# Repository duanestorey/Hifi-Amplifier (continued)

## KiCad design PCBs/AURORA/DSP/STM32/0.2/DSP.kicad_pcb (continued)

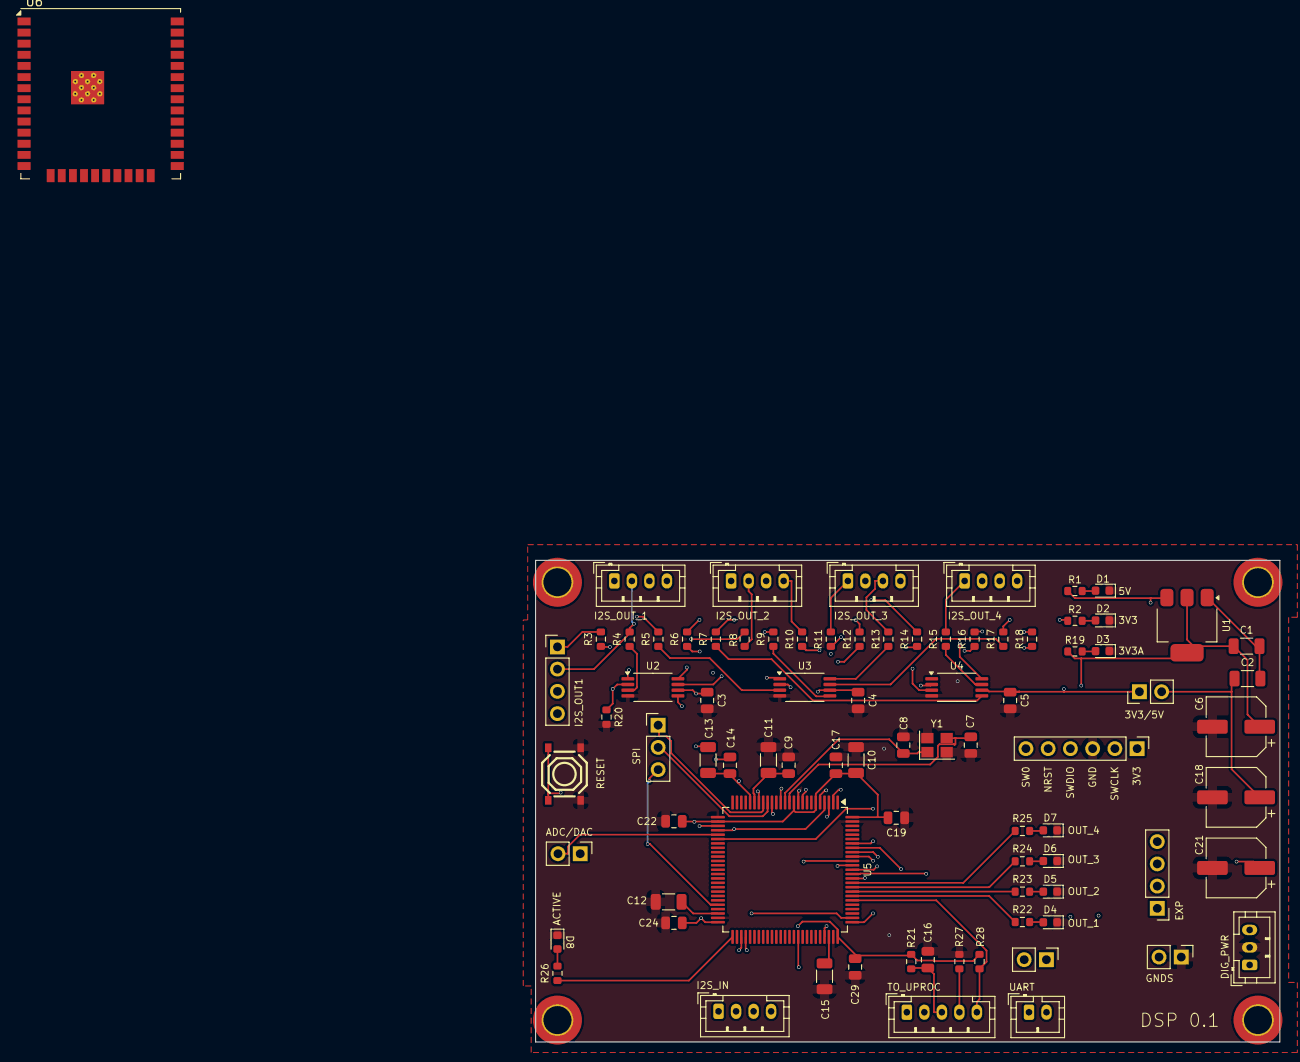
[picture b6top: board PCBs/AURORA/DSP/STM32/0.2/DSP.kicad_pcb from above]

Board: 4 copper layers, 85.0 x 55.0 mm, 87 parts (0 on the bottom side), 81 nets.

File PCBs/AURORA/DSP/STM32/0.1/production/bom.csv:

Designator,Footprint,Quantity,Value,LCSC Part #
"C1, C10, C11, C13, C2",1206,5,10u,C13585
"C12, C15",1206,2,2.2u,C50254
"C14, C16, C17, C19, C22, C24, C29, C3, C4, C5, C9",0805,11,0.1u,C28233
"C18, C21, C6",CP_Elec_6.3x7.7,3,220u,C4747974
"C7, C8",0805,2,20p,C1798
"D1, D2, D3, D4, D5, D6, D7, D8",0805,8,BLUE,C84259
"J1, J2, J3, J4, J7",JST_PH_B4B-PH-K_1x04_P2.00mm_Vertical,5,Conn_01x04_Pin,
"J10, J9",JST_PH_B2B-PH-K_1x02_P2.00mm_Vertical,2,Conn_01x02_Male,
"J11, J14, J15, J16, J17",PinHeader_1x02_P2.54mm_Vertical,5,Conn_01x02_Pin,C225477
"J12, J13, J18",PinHeader_1x04_P2.54mm_Vertical,3,Conn_01x04_Pin,C6332197
J5,PinHeader_1x06_P2.54mm_Vertical,1,Conn_01x06_Pin,C6332199
"J6, J8",JST_PH_B3B-PH-K_1x03_P2.00mm_Vertical,2,Conn_01x03_Pin,
"R1, R19, R2, R22, R23, R24, R25, R26",0603,8,150R,C22808
"R10, R11, R12, R13, R14, R15, R16, R17, R18, R3, R4, R5, R6, R7, R8, R9",0603,16,22R,C23345
"R20, R21, R27, R28",0603,4,4.7K,C23162
SW2,SW-SMD_4P-L5.1-W5.1-P3.70-LS6.5-TL_H1.5,1,TS-1187A-B-A-B,C318884
U1,SOT-223-3_TabPin2,1,AMS1117-3.3,C6186
"U2, U3, U4",TSSOP-8_4.4x3mm_P0.65mm,3,PI6CV304,C2649345
U5,LQFP-100_14x14mm_P0.5mm,1,STM32H723VGTx,C730142
Y1,Crystal_SMD_SeikoEpson_FA238-4Pin_3.2x2.5mm,1,25 MHz,C9006

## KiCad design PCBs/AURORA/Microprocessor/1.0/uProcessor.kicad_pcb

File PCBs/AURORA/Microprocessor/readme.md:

# Microprocessor Board

The heart of the amplifier is this microprocessor board based on the ESP32 WROOM 32 IC. Now supports a HAT.

## Version History

- 1.0: Initial Release
- 1.1: Addressed issue with ESP32 programming transistors
- 1.2: Added missing pull-down resistor for relay/softstart 

## Speciality Components

* ESP32 WROOM 32
* FT232RL USB to UART converter
* TMP100 temperature sensor

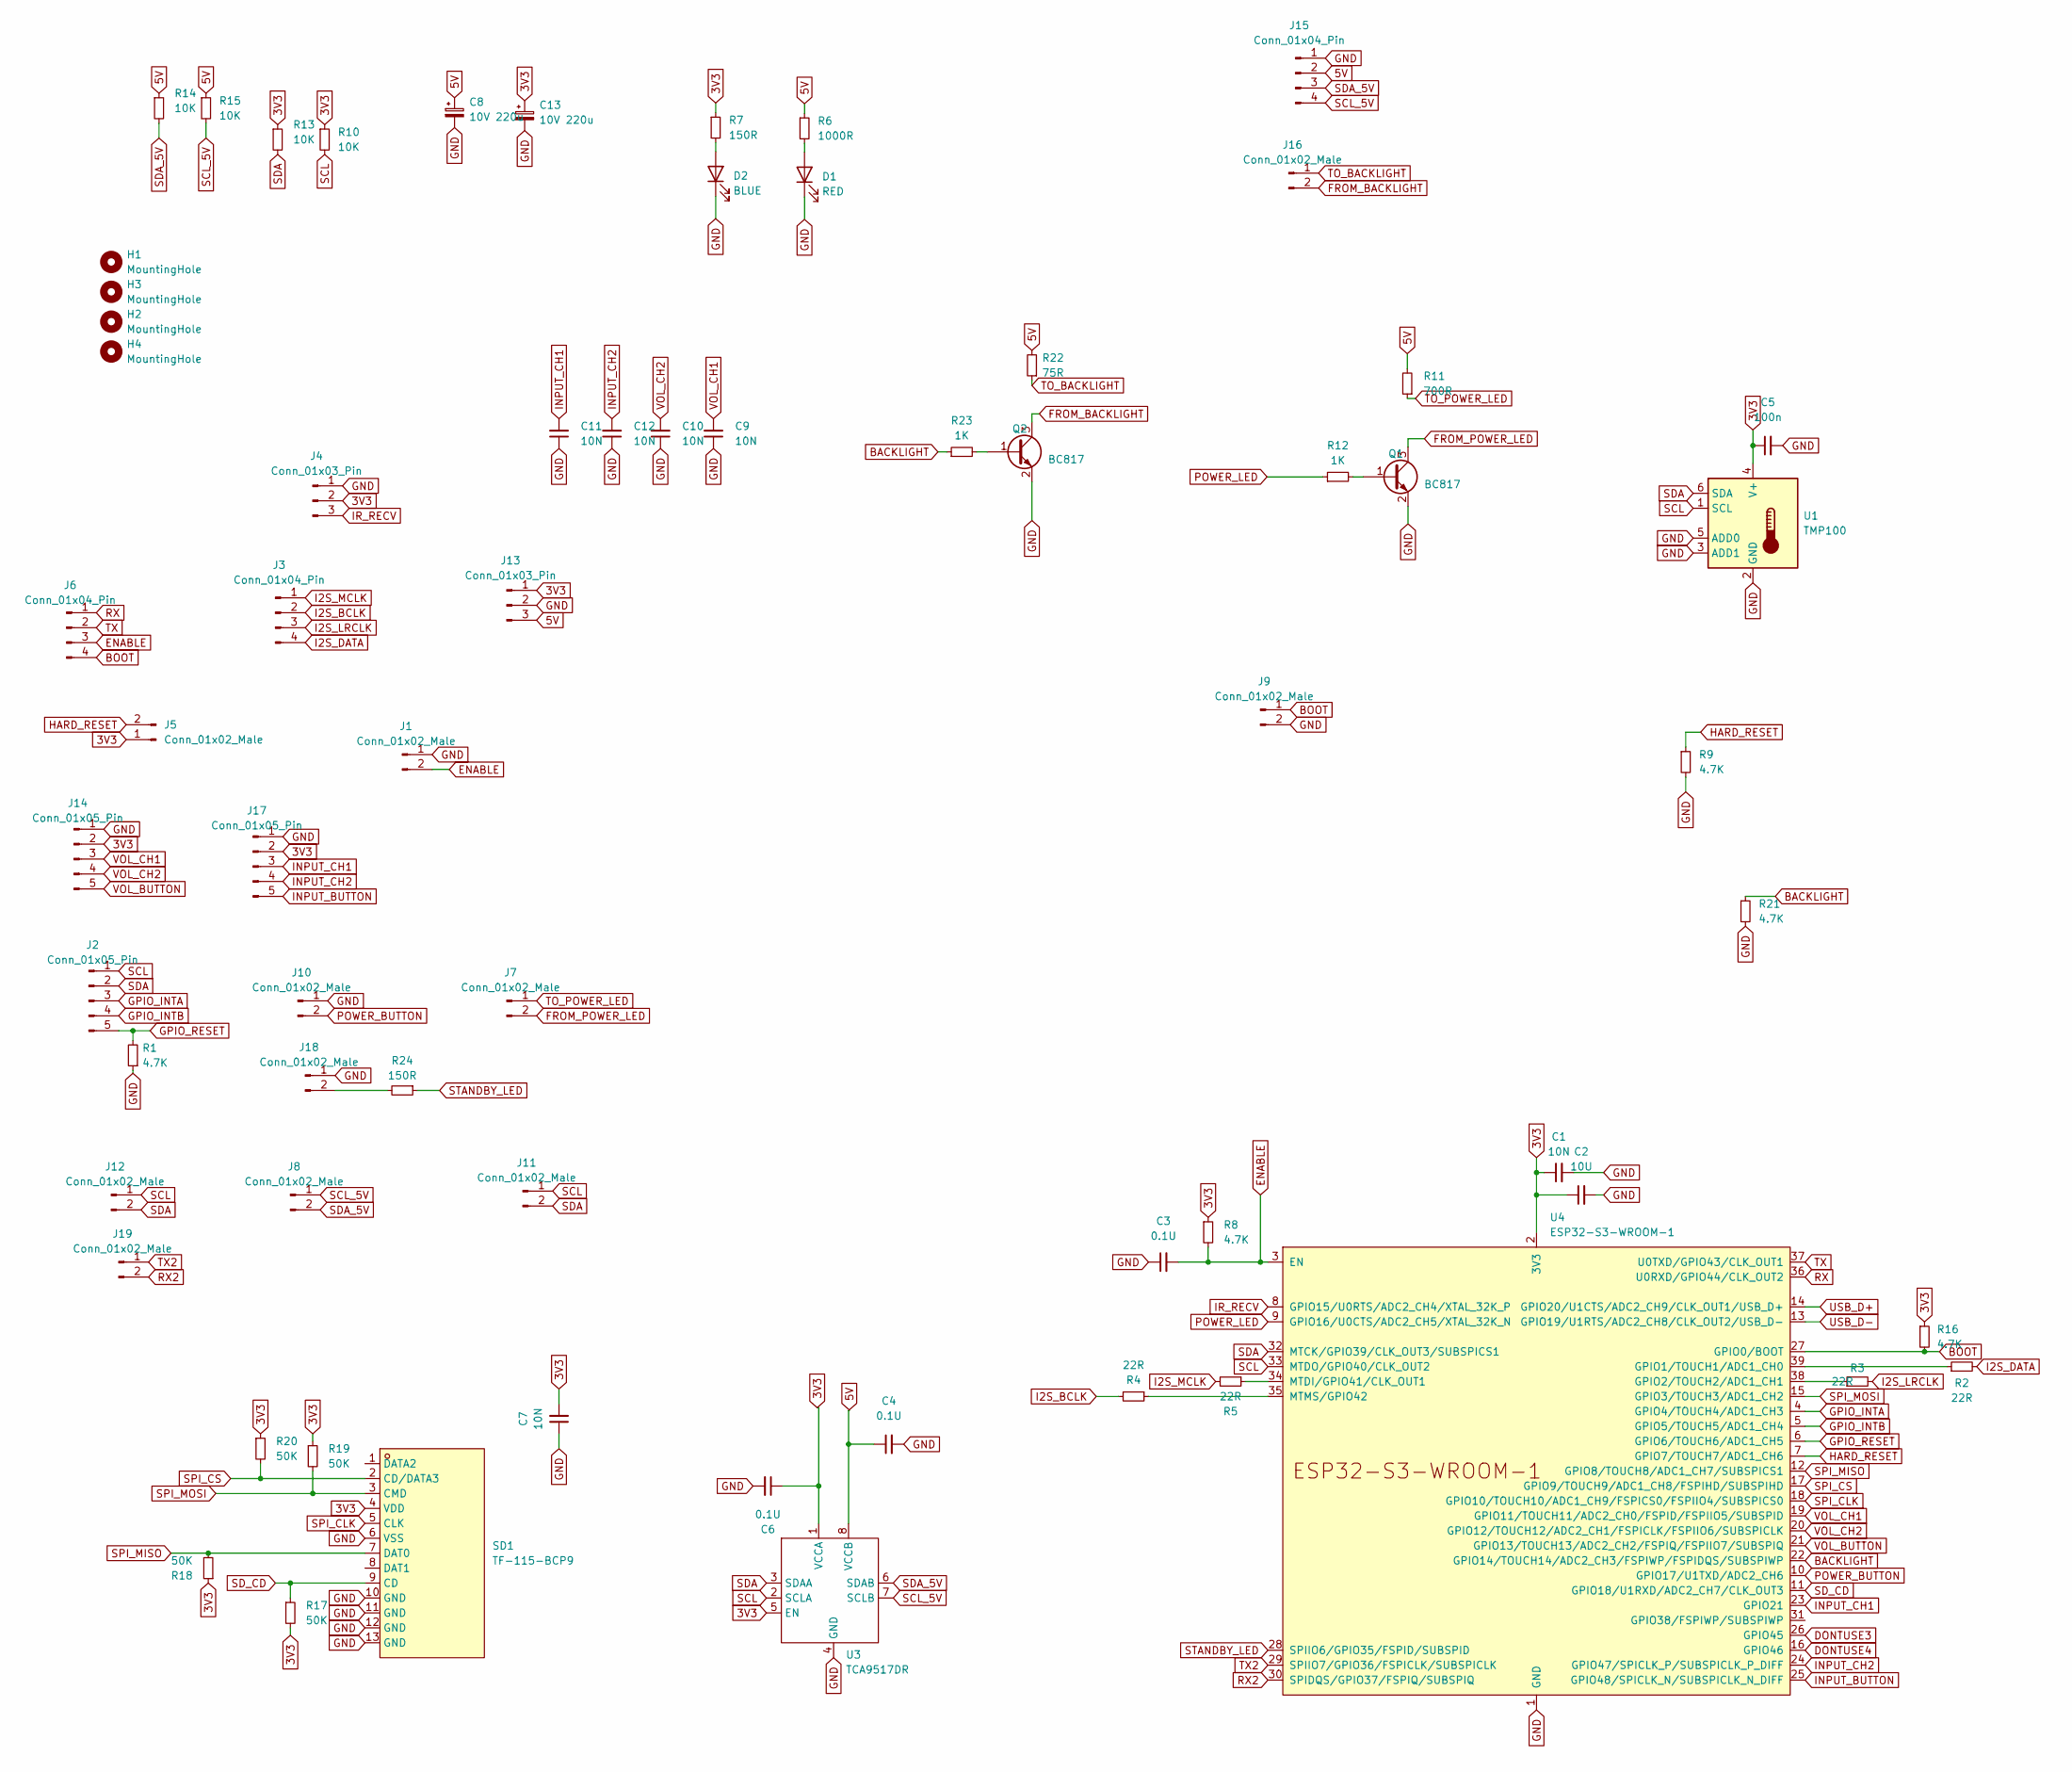
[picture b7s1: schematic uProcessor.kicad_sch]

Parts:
C1, C7: 10N; C_0805_2012Metric_Pad1.18x1.45mm_HandSolder
C2: 10U; C_1206_3216Metric_Pad1.33x1.80mm_HandSolder
C3, C4, C6: 0.1U; C_0805_2012Metric_Pad1.18x1.45mm_HandSolder
C5: 100n; C_0805_2012Metric_Pad1.18x1.45mm_HandSolder
C8, C13: 10V 220u; CP_Radial_D6.3mm_P2.50mm
C9, C10, C11, C12: 10N; C_0603_1608Metric_Pad1.08x0.95mm_HandSolder
D1: RED; LED_0603_1608Metric; LCSC XL-1608UBC-04
D2: BLUE; LED_0603_1608Metric; LCSC NCD0603R1
H1, H2, H3, H4: MountingHole; MountingHole_3.2mm_M3_DIN965_Pad_TopOnly
J1, J7, J8, J10, J11, J12, J16, J18, J19: Conn_01x02_Male; JST_PH_B2B-PH-K_1x02_P2.00mm_Vertical
J2, J14, J17: Conn_01x05_Pin; JST_PH_B5B-PH-K_1x05_P2.00mm_Vertical
J3, J6, J15: Conn_01x04_Pin; JST_PH_B4B-PH-K_1x04_P2.00mm_Vertical
J4, J13: Conn_01x03_Pin; JST_PH_B3B-PH-K_1x03_P2.00mm_Vertical
J5, J9: Conn_01x02_Male; PinHeader_1x02_P2.54mm_Vertical
Q1, Q2: BC817; TSOT-23; Mouser 637-BC817K-40
R1, R8, R9, R16, R21: 4.7K; R_0603_1608Metric_Pad0.98x0.95mm_HandSolder
R2, R3, R4, R5: 22R; R_0603_1608Metric; Mouser 603-RT0805FRE0722RL
R6: 1000R; R_0603_1608Metric_Pad0.98x0.95mm_HandSolder
R7, R24: 150R; R_0603_1608Metric_Pad0.98x0.95mm_HandSolder
R10, R13, R14, R15: 10K; R_0603_1608Metric_Pad0.98x0.95mm_HandSolder
R11: 700R; R_0603_1608Metric_Pad0.98x0.95mm_HandSolder
R12, R23: 1K; R_0603_1608Metric_Pad0.98x0.95mm_HandSolder
R17, R18, R19, R20: 50K; R_0603_1608Metric_Pad0.98x0.95mm_HandSolder
R22: 75R; R_0603_1608Metric_Pad0.98x0.95mm_HandSolder
SD1: TF-115-BCP9; TF-SMD_TF-115-BCP9; LCSC Part C720505
U1: TMP100; SOT-23-6
U3: TCA9517DR; SOIC-8_3.9x4.9mm_P1.27mm; Mouser 595-TCA9517DR
U4: ESP32-S3-WROOM-1

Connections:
3V3: C1.1, C2.1, C5.1, C6.1, C7.2, C13.1, J4.2, J5.1, J13.1, J14.2, J17.2, R7.1, R8.1, R10.1, R13.1, R16.1, R17.2, R18.1, R19.1, R20.1, SD1.4 (VDD), U1.4 (V+), U3.1 (VCCA), U3.5 (EN), U4.2 (3V3)
5V: C4.1, C8.1, J13.3, J15.2, R6.1, R11.2, R14.1, R15.1, R22.2, U3.8 (VCCB)
BACKLIGHT: R21.1, R23.1, U4.22 (GPIO14/TOUCH14/ADC2_CH3/FSPIWP/FSPIDQS/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)
BOOT: J6.4, J9.1, R16.2, U4.27 (GPIO0/BOOT)
DONTUSE3: U4.26 (GPIO45)
DONTUSE4: U4.16 (GPIO46)
ENABLE: C3.2, J1.2, J6.3, R8.2, U4.3 (EN)
FROM_BACKLIGHT: J16.2, Q2.3 (C)
FROM_POWER_LED: J7.2, Q1.3 (C)
GND: C1.2, C2.2, C3.1, C4.2, C5.2, C6.2, C7.1, C8.2, C9.1, C10.1, C11.1, C12.1, C13.2, D1.1 (K), D2.1 (K), J1.1, J4.1, J9.2, J10.1, J13.2, J14.1, J15.1, J17.1, J18.1, Q1.2 (E), Q2.2 (E), R1.1, R9.2, R21.2, SD1.6 (VSS), SD1.10 (GND), SD1.11 (GND), SD1.12 (GND), SD1.13 (GND), U1.2 (GND), U1.3 (ADD1), U1.5 (ADD0), U3.4 (GND), U4.1 (GND), U4.40 (GND), U4.41 (GND)
GPIO_INTA: J2.3, U4.4 (GPIO4/TOUCH4/ADC1_CH3)
GPIO_INTB: J2.4, U4.5 (GPIO5/TOUCH5/ADC1_CH4)
GPIO_RESET: J2.5, R1.2, U4.6 (GPIO6/TOUCH6/ADC1_CH5)
HARD_RESET: J5.2, R9.1, U4.7 (GPIO7/TOUCH7/ADC1_CH6)
I2S_BCLK: J3.2, R4.2
I2S_DATA: J3.4, R2.2
I2S_LRCLK: J3.3, R3.2
I2S_MCLK: J3.1, R5.2
INPUT_BUTTON: J17.5, U4.25 (GPIO48/SPICLK_N/SUBSPICLK_N_DIFF)
INPUT_CH1: C11.2, J17.3, U4.23 (GPIO21)
INPUT_CH2: C12.2, J17.4, U4.24 (GPIO47/SPICLK_P/SUBSPICLK_P_DIFF)
IR_RECV: J4.3, U4.8 (GPIO15/U0RTS/ADC2_CH4/XTAL_32K_P)
unnamed: D1.2 (A), R6.2
unnamed: D2.2 (A), R7.2
unnamed: J18.2, R24.2
unnamed: Q1.1 (B), R12.2
unnamed: Q2.1 (B), R23.2
unnamed: R2.1, U4.39 (GPIO1/TOUCH1/ADC1_CH0)
unnamed: R3.1, U4.38 (GPIO2/TOUCH2/ADC1_CH1)
unnamed: R5.1, U4.34 (MTDI/GPIO41/CLK_OUT1)
unnamed: R4.1, U4.35 (MTMS/GPIO42)
POWER_BUTTON: J10.2, U4.10 (GPIO17/U1TXD/ADC2_CH6)
POWER_LED: R12.1, U4.9 (GPIO16/U0CTS/ADC2_CH5/XTAL_32K_N)
RX: J6.1, U4.36 (U0RXD/GPIO44/CLK_OUT2)
RX2: J19.2, U4.30 (SPIDQS/GPIO37/FSPIQ/SUBSPIQ)
SCL: J2.1, J11.1, J12.1, R10.2, U1.1 (SCL), U3.2 (SCLA), U4.33 (MTDO/GPIO40/CLK_OUT2)
SCL_5V: J8.1, J15.4, R15.2, U3.7 (SCLB)
SDA: J2.2, J11.2, J12.2, R13.2, U1.6 (SDA), U3.3 (SDAA), U4.32 (MTCK/GPIO39/CLK_OUT3/SUBSPICS1)
SDA_5V: J8.2, J15.3, R14.2, U3.6 (SDAB)
SD_CD: R17.1, SD1.9 (CD), U4.11 (GPIO18/U1RXD/ADC2_CH7/CLK_OUT3)
SPI_CLK: SD1.5 (CLK), U4.18 (GPIO10/TOUCH10/ADC1_CH9/FSPICS0/FSPIIO4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)
SPI_CS: R20.2, SD1.2 (CD/DATA3), U4.17 (GPIO9/TOUCH9/ADC1_CH8/FSPIHD/SUBSPIHD)
SPI_MISO: R18.2, SD1.7 (DAT0), U4.12 (GPIO8/TOUCH8/ADC1_CH7/SUBSPICS1)
SPI_MOSI: R19.2, SD1.3 (CMD), U4.15 (GPIO3/TOUCH3/ADC1_CH2)
STANDBY_LED: R24.1, U4.28 (SPIIO6/GPIO35/FSPID/SUBSPID)
TO_BACKLIGHT: J16.1, R22.1
TO_POWER_LED: J7.1, R11.1
TX: J6.2, U4.37 (U0TXD/GPIO43/CLK_OUT1)
TX2: J19.1, U4.29 (SPIIO7/GPIO36/FSPICLK/SUBSPICLK)
USB_D+: U4.14 (GPIO20/U1CTS/ADC2_CH9/CLK_OUT1/USB_D+)
USB_D-: U4.13 (GPIO19/U1RTS/ADC2_CH8/CLK_OUT2/USB_D-)
VOL_BUTTON: J14.5, U4.21 (GPIO13/TOUCH13/ADC2_CH2/FSPIQ/FSPIIO7/S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)
VOL_CH1: C9.2, J14.3, U4.19 (GPIO11/TOUCH11/ADC2_CH0/FSPID/FSPIIO5/S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)
VOL_CH2: C10.2, J14.4, U4.20 (GPIO12/TOUCH12/ADC2_CH1/FSPICLK/FSPIIO6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)

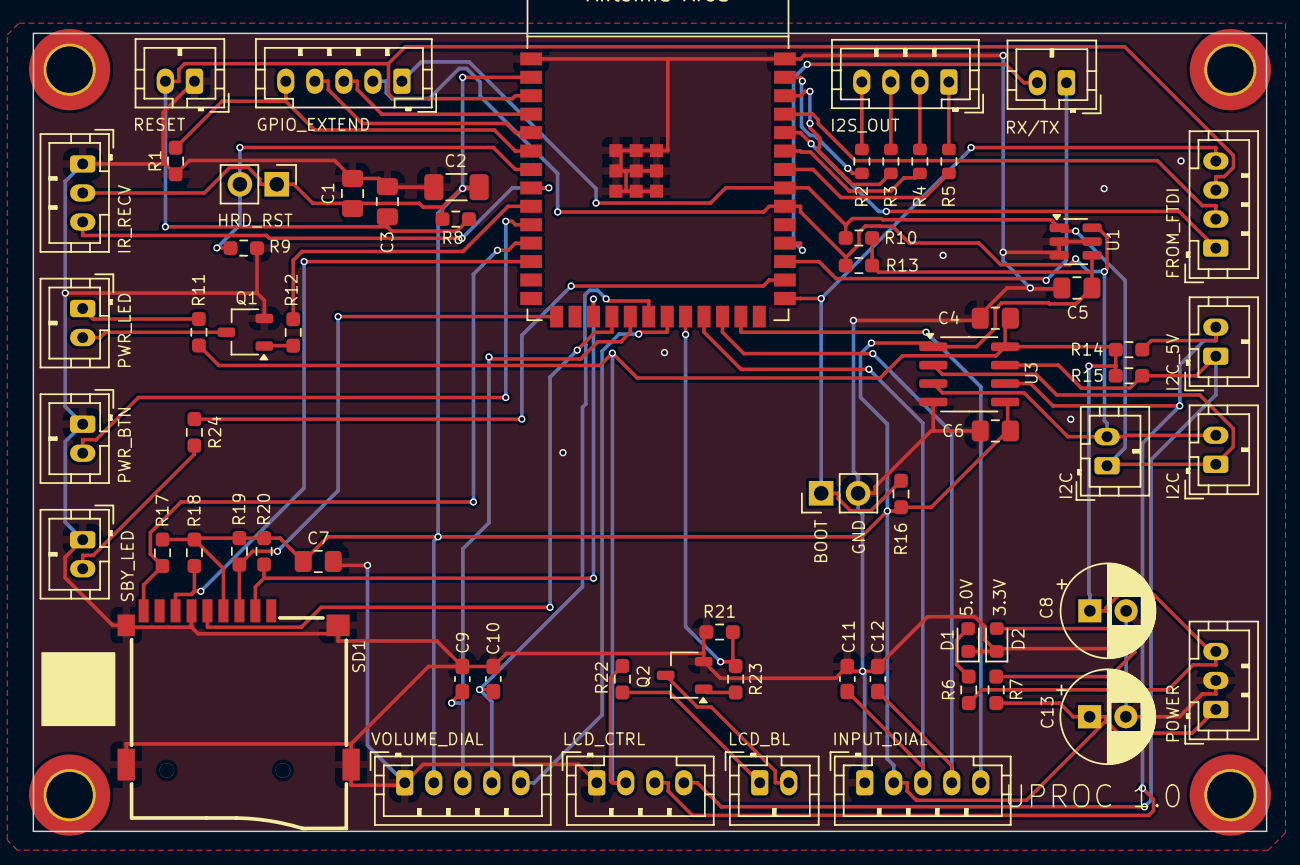
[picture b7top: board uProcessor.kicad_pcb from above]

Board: 2 copper layers, 85.0 x 55.0 mm, 68 parts (0 on the bottom side), 50 nets.

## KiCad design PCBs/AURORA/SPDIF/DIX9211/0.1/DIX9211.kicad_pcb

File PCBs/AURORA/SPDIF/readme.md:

## Subwoofer

This PCB generates a subwoofer signal from the left and right channels. A jumper is available to pass the left and right channels directly, or to filter out the 
bass being sent to the subwoofer as well.  The current crossover frequency is set to 80 Hz.

### Version History

- 1.0: Initial Release

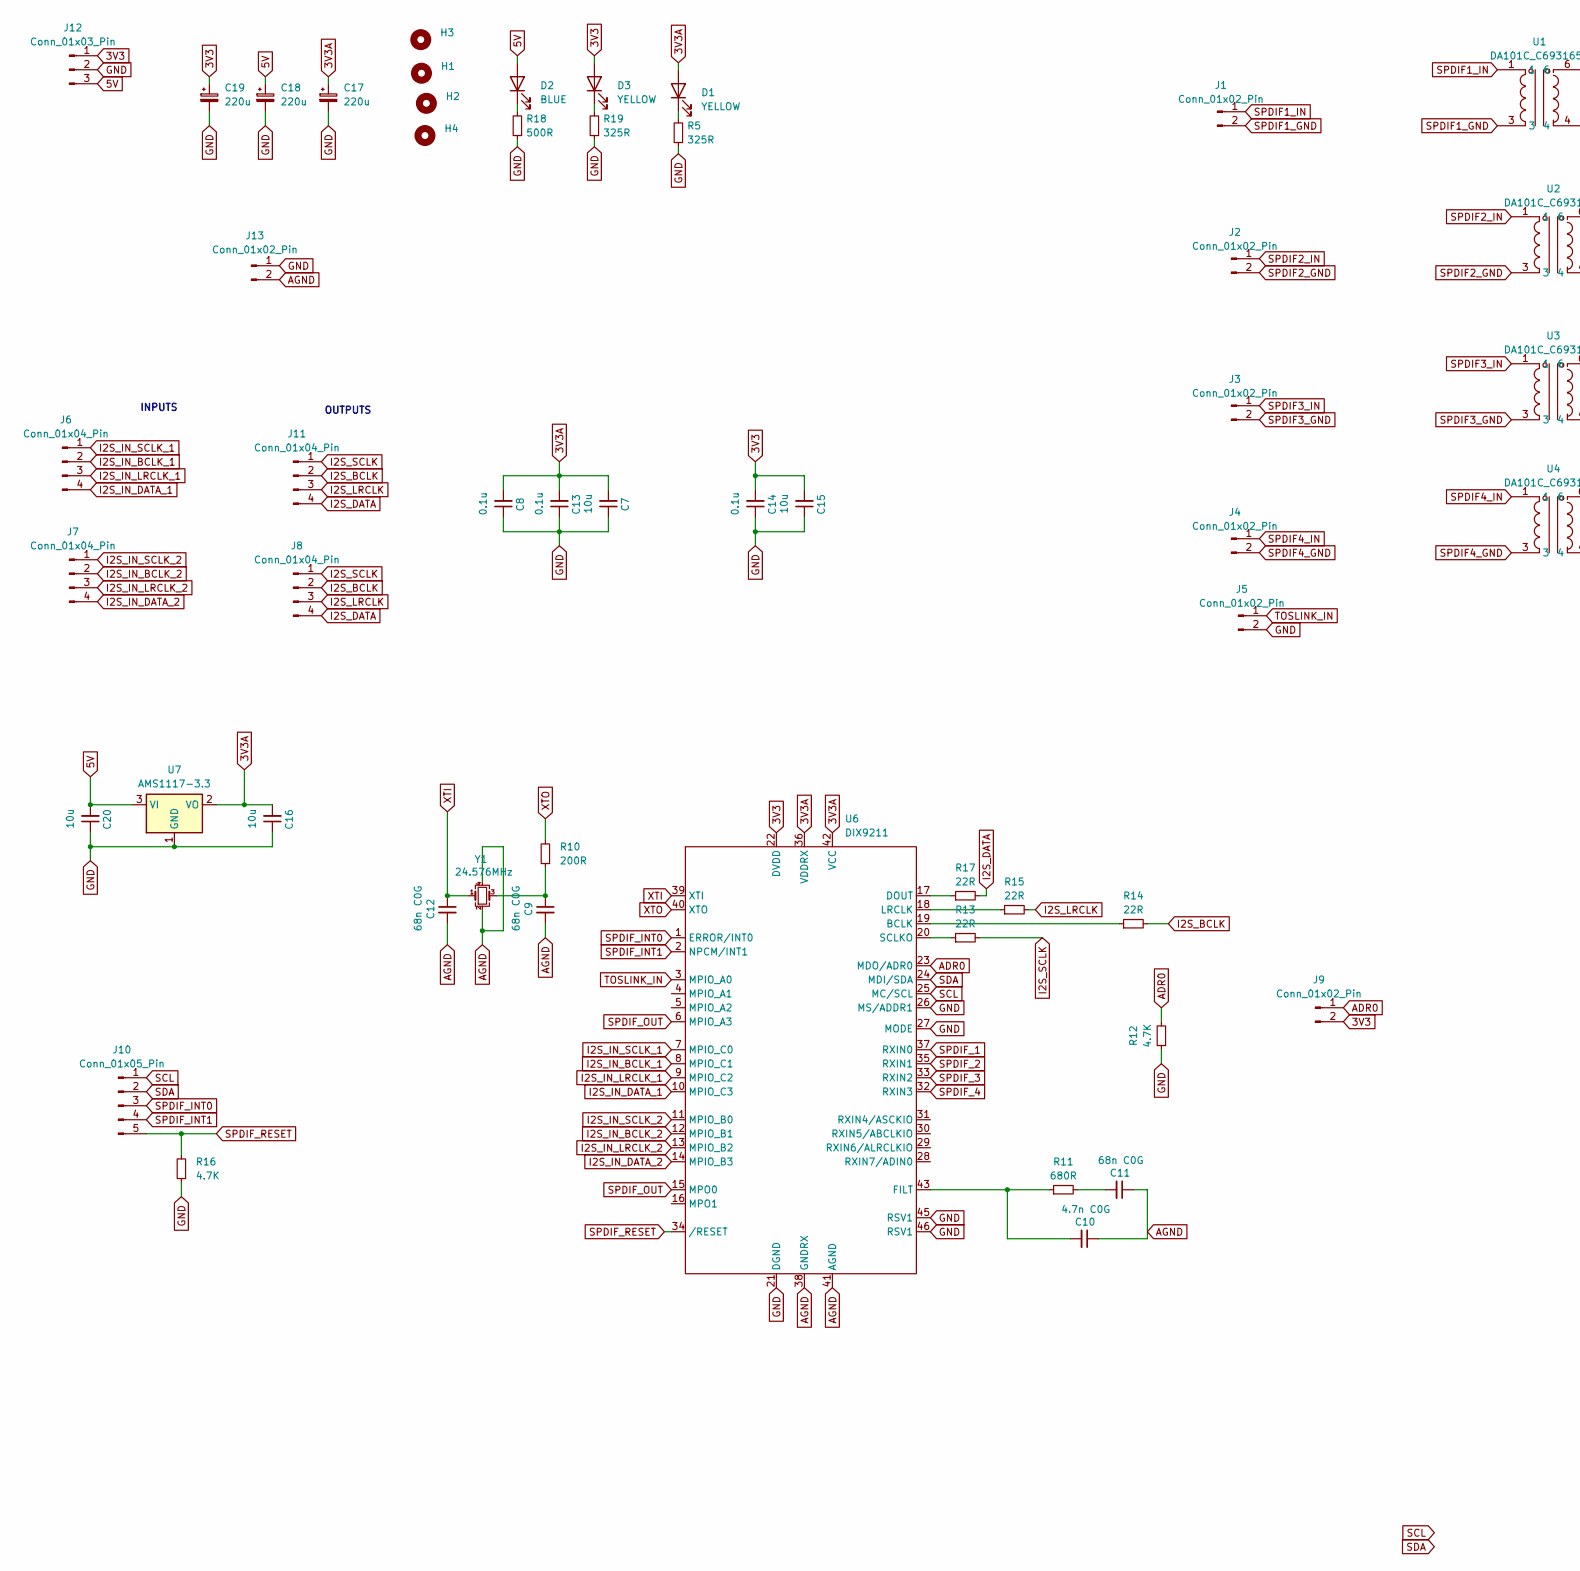
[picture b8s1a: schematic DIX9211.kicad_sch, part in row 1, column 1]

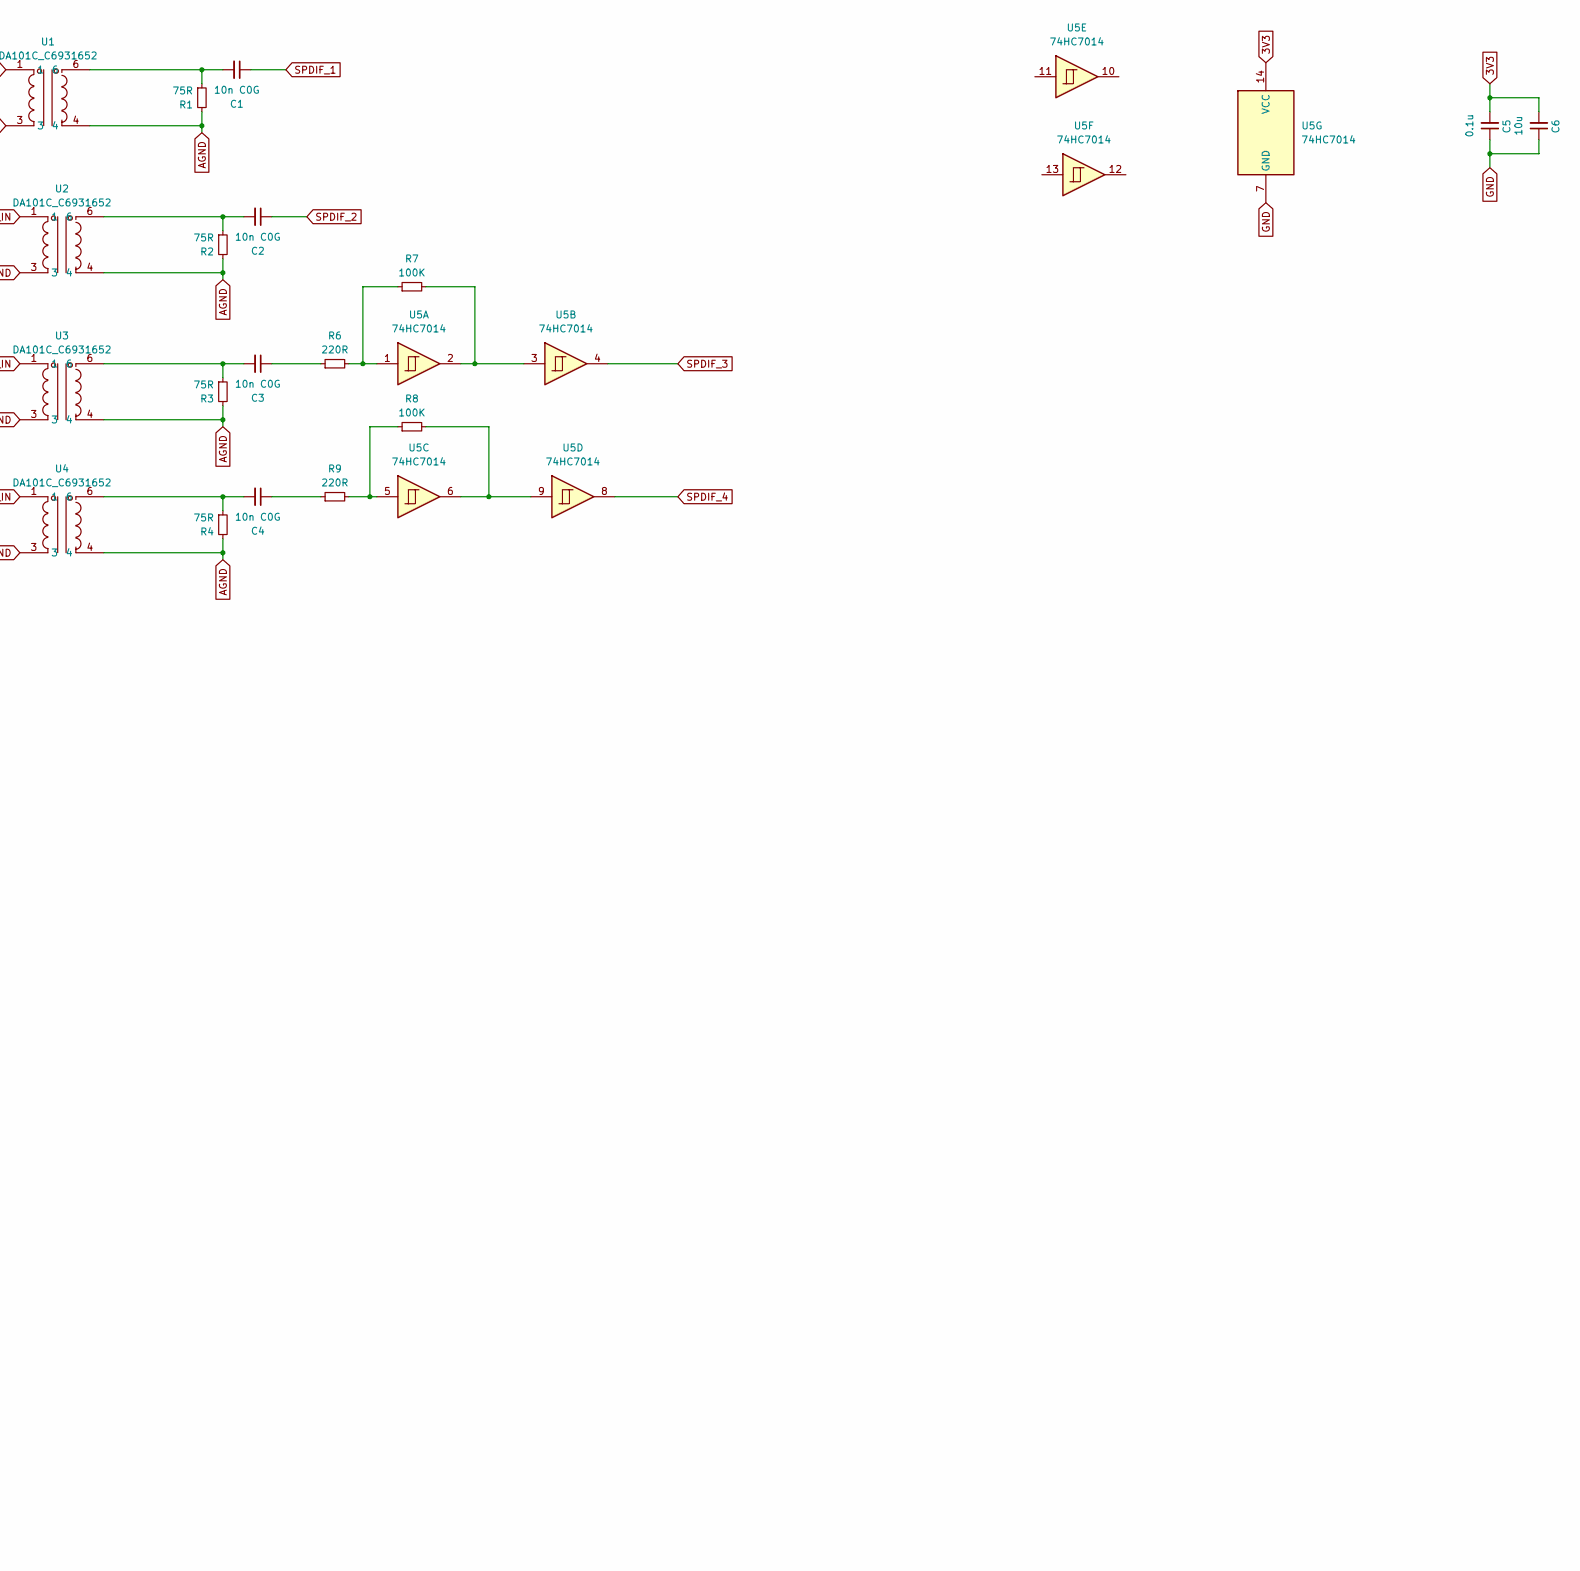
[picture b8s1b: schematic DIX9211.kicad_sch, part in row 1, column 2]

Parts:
C1, C2, C3, C4: 10n C0G; C_0805_2012Metric_Pad1.18x1.45mm_HandSolder; Mouser 791-0805N103G250CT
C5, C8, C13, C14: 0.1u; C_0805_2012Metric_Pad1.18x1.45mm_HandSolder
C6, C7, C15, C16, C20: 10u; C_1206_3216Metric_Pad1.33x1.80mm_HandSolder
C9, C11, C12: 68n C0G; C_0603_1608Metric
C10: 4.7n C0G; C_0603_1608Metric
C17, C18, C19: 220u; CP_Radial_D6.3mm_P2.50mm
D1, D3: YELLOW; LED_0603_1608Metric
D2: BLUE; LED_0603_1608Metric
H1, H2, H3, H4: MountingHole; MountingHole_3.2mm_M3_DIN965_Pad_TopOnly
J1, J2, J3, J4, J5: Conn_01x02_Pin; JST_XH_B2B-XH-A_1x02_P2.50mm_Vertical
J6, J7, J11: Conn_01x04_Pin; JST_PH_B4B-PH-K_1x04_P2.00mm_Vertical
J8: Conn_01x04_Pin; PinHeader_1x04_P2.54mm_Vertical
J9, J13: Conn_01x02_Pin; PinHeader_1x02_P2.54mm_Vertical
J10: Conn_01x05_Pin; JST_PH_B5B-PH-K_1x05_P2.00mm_Vertical
J12: Conn_01x03_Pin; JST_PH_B3B-PH-K_1x03_P2.00mm_Vertical
R1, R2, R3, R4: 75R; R_0603_1608Metric_Pad0.98x0.95mm_HandSolder; Mouser 71-CRCW0603-75-E3
R5, R19: 325R; R_0603_1608Metric_Pad0.98x0.95mm_HandSolder
R6, R9: 220R; R_0603_1608Metric_Pad0.98x0.95mm_HandSolder; Mouser 71-CRCW0603-75-E3
R7, R8: 100K; R_0603_1608Metric_Pad0.98x0.95mm_HandSolder; Mouser 71-CRCW0603-75-E3
R10: 200R; R_0603_1608Metric
R11: 680R; R_0603_1608Metric
R12, R16: 4.7K; R_0603_1608Metric
R13, R14, R15, R17: 22R; R_0603_1608Metric
R18: 500R; R_0603_1608Metric_Pad0.98x0.95mm_HandSolder
U1, U2, U3, U4: DA101C_C6931652; XFMR-TH_4P-L9.5-W9.0-P5.08-LS10.2_C9900096976; LCSC Part C6931652
U5: 74HC7014; TSSOP-14_4.4x5mm_P0.65mm
U6: DIX9211; LQFP-48_7x7mm_P0.5mm; Mouser 595-DIX9211PTR
U7: AMS1117-3.3; SOT-223-3_TabPin2
Y1: 24.576MHz; Crystal_SMD_SeikoEpson_FA238-4Pin_3.2x2.5mm

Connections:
3V3: C5.2, C6.2, C14.2, C15.2, C19.1, D3.2 (A), J9.2, J12.1, U5.14 (VCC), U6.22 (DVDD)
3V3A: C7.2, C8.2, C13.2, C16.2, C17.1, D1.2 (A), U6.36 (VDDRX), U6.42 (VCC), U7.2 (VO)
5V: C18.1, C20.2, D2.2 (A), J12.3, U7.3 (VI)
ADR0: J9.1, R12.2, U6.23 (MDO/ADR0)
AGND: C9.2, C10.1, C11.1, C12.2, J13.2, R1.2, R2.2, R3.2, R4.2, U1.4, U2.4, U3.4, U4.4, U6.38 (GNDRX), U6.41 (AGND), Y1.2, Y1.4
GND: C5.1, C6.1, C7.1, C8.1, C13.1, C14.1, C15.1, C16.1, C17.2, C18.2, C19.2, C20.1, J5.2, J12.2, J13.1, R5.1, R12.1, R16.1, R18.1, R19.1, U5.7 (GND), U6.21 (DGND), U6.26 (MS/ADDR1), U6.27 (MODE), U6.45 (RSV1), U6.46 (RSV1), U7.1 (GND)
I2S_BCLK: J8.2, J11.2, R14.2
I2S_DATA: J8.4, J11.4, R17.2
I2S_IN_BCLK_1: J6.2, U6.8 (MPIO_C1)
I2S_IN_BCLK_2: J7.2, U6.12 (MPIO_B1)
I2S_IN_DATA_1: J6.4, U6.10 (MPIO_C3)
I2S_IN_DATA_2: J7.4, U6.14 (MPIO_B3)
I2S_IN_LRCLK_1: J6.3, U6.9 (MPIO_C2)
I2S_IN_LRCLK_2: J7.3, U6.13 (MPIO_B2)
I2S_IN_SCLK_1: J6.1, U6.7 (MPIO_C0)
I2S_IN_SCLK_2: J7.1, U6.11 (MPIO_B0)
I2S_LRCLK: J8.3, J11.3, R15.2
I2S_SCLK: J8.1, J11.1, R13.2
unnamed: C1.2, R1.1, U1.6
unnamed: C2.2, R2.1, U2.6
unnamed: C3.1, R6.1
unnamed: C3.2, R3.1, U3.6
unnamed: C4.1, R9.1
unnamed: C4.2, R4.1, U4.6
unnamed: C9.1, R10.1, Y1.3
unnamed: C11.2, R11.2
unnamed: D1.1 (K), R5.2
unnamed: D2.1 (K), R18.2
unnamed: D3.1 (K), R19.2
unnamed: R6.2, R7.1, U5.1
unnamed: R7.2, U5.2, U5.3
unnamed: R8.1, R9.2, U5.5
unnamed: R8.2, U5.6, U5.9
unnamed: R14.1, U6.19 (BCLK)
unnamed: R17.1, U6.17 (DOUT)
unnamed: C10.2, R11.1, U6.43 (FILT)
unnamed: R15.1, U6.18 (LRCLK)
unnamed: R13.1, U6.20 (SCLKO)
SCL: J10.1, U6.25 (MC/SCL)
SDA: J10.2, U6.24 (MDI/SDA)
SPDIF1_GND: J1.2, U1.3
SPDIF1_IN: J1.1, U1.1
SPDIF2_GND: J2.2, U2.3
SPDIF2_IN: J2.1, U2.1
SPDIF3_GND: J3.2, U3.3
SPDIF3_IN: J3.1, U3.1
SPDIF4_GND: J4.2, U4.3
SPDIF4_IN: J4.1, U4.1
SPDIF_1: C1.1, U6.37 (RXIN0)
SPDIF_2: C2.1, U6.35 (RXIN1)
SPDIF_3: U5.4, U6.33 (RXIN2)
SPDIF_4: U5.8, U6.32 (RXIN3)
SPDIF_INT0: J10.3, U6.1 (ERROR/INT0)
SPDIF_INT1: J10.4, U6.2 (NPCM/INT1)
SPDIF_OUT: U6.6 (MPIO_A3), U6.15 (MPO0)
SPDIF_RESET: J10.5, R16.2, U6.34 (/RESET)
TOSLINK_IN: J5.1, U6.3 (MPIO_A0)
XTI: C12.1, U6.39 (XTI), Y1.1
XTO: R10.2, U6.40 (XTO)

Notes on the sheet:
OUTPUTS
INPUTS

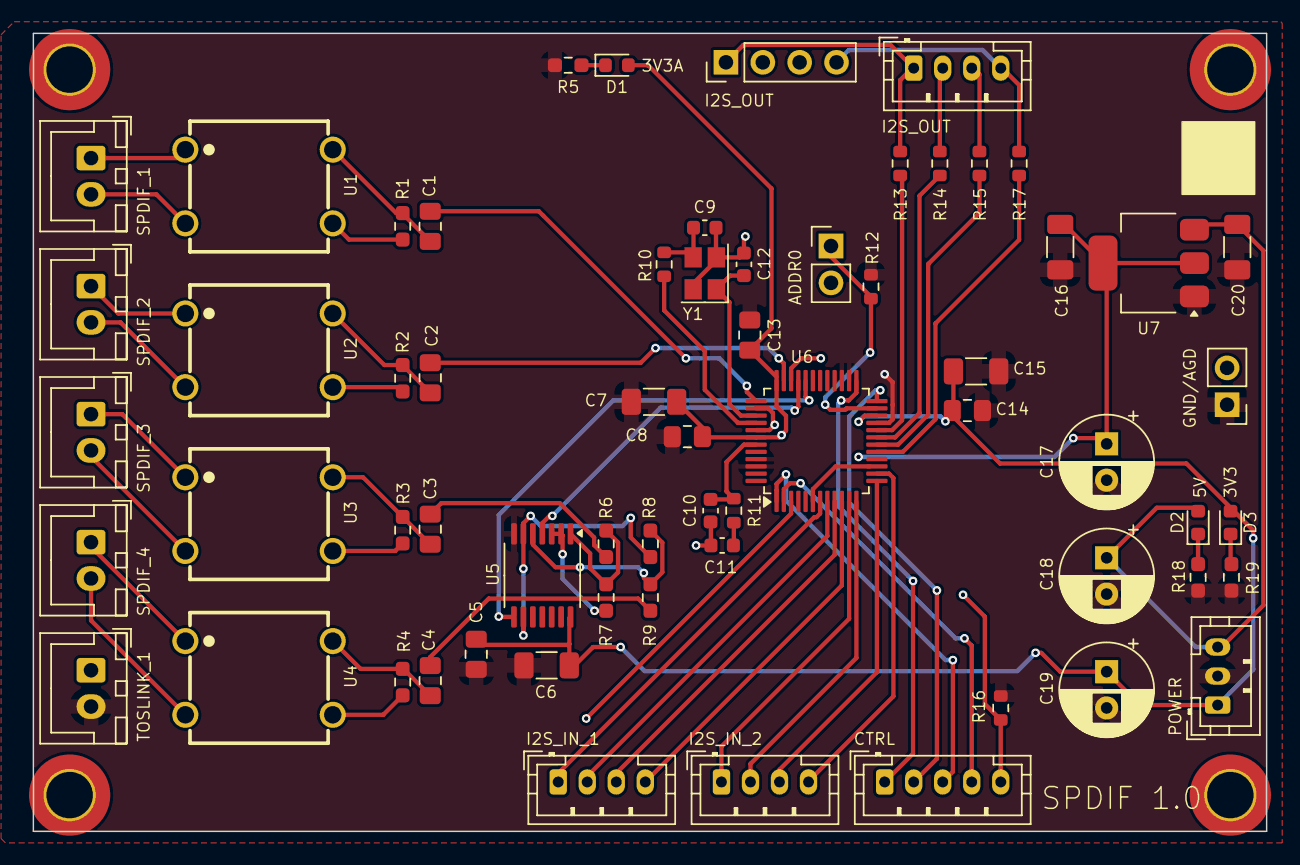
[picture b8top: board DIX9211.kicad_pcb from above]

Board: 4 copper layers, 85.0 x 55.0 mm, 67 parts (0 on the bottom side), 59 nets.

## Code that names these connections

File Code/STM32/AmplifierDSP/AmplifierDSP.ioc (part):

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Mcu.Name=STM32H723VGTx
Mcu.Package=LQFP100
Mcu.UserName=STM32H723VGTx
PA13(JTMS/SWDIO).Mode=Trace_Asynchronous_SW
PA13(JTMS/SWDIO).Signal=DEBUG_JTMS-SWDIO
PA14(JTCK/SWCLK).Mode=Trace_Asynchronous_SW
PA14(JTCK/SWCLK).Signal=DEBUG_JTCK-SWCLK
PA15(JTDI).Mode=Full_Duplex_Slave
PA15(JTDI).Signal=I2S1_WS
PA4.Signal=COMP_DAC11_group
PA5.Mode=Full_Duplex_Slave
PA5.Signal=I2S1_CK
PA6.Signal=ADCx_INP3
PA7.Mode=Full_Duplex_Slave
PA7.Signal=I2S1_SDO
PB10.Mode=Full_Duplex_Master
PB10.Signal=SPI2_SCK
PB12.GPIOParameters=GPIO_PuPd,GPIO_Label
PB12.GPIO_Label=DSP_ACTIVE
PB12.GPIO_PuPd=GPIO_PULLDOWN
PB12.Signal=GPIO_Output
PB14.Mode=Asynchronous
PB14.Signal=USART1_TX
PB15.Mode=Asynchronous
PB15.Signal=USART1_RX
PB3(JTDO/TRACESWO).Mode=Trace_Asynchronous_SW
PB3(JTDO/TRACESWO).Signal=DEBUG_JTDO-SWO
PB4(NJTRST).Mode=Full_Duplex_Slave
PB4(NJTRST).Signal=I2S1_SDI
PB6.Mode=I2C
PB6.Signal=I2C1_SCL
PB7.Mode=I2C
PB7.Signal=I2C1_SDA
PC1.Mode=SAI_A_SyncSlave
PC1.Signal=SAI4_SD_A
PC15-OSC32_OUT.GPIOParameters=GPIO_PuPd,GPIO_Label
PC15-OSC32_OUT.GPIO_Label=DSP_CLOCKS_EN
PC15-OSC32_OUT.GPIO_PuPd=GPIO_PULLDOWN
PC15-OSC32_OUT.Signal=GPIO_Output
PC2_C.Mode=Full_Duplex_Master
PC2_C.Signal=SPI2_MISO
PC3_C.Mode=Full_Duplex_Master
PC3_C.Signal=SPI2_MOSI
PC9.Mode=Audio_ClockIn
PC9.Signal=I2S_CKIN
PD1.GPIOParameters=GPIO_PuPd,GPIO_Label
PD1.GPIO_Label=DSP_LEFT
PD1.GPIO_PuPd=GPIO_PULLDOWN
PD1.Signal=GPIO_Output
PD2.GPIOParameters=GPIO_PuPd,GPIO_Label
PD2.GPIO_Label=DSP_RIGHT
PD2.GPIO_PuPd=GPIO_PULLDOWN
PD2.Signal=GPIO_Output
PD3.GPIOParameters=GPIO_PuPd,GPIO_Label
PD3.GPIO_Label=DSP_SW
PD3.GPIO_PuPd=GPIO_PULLDOWN
PD3.Signal=GPIO_Output
PD4.GPIOParameters=GPIO_PuPd,GPIO_Label
PD4.GPIO_Label=DSP_ALT
PD4.GPIO_PuPd=GPIO_PULLDOWN
PD4.Signal=GPIO_Output
PE3.Mode=SAI_B_SyncSlave
PE3.Signal=SAI1_SD_B
PE4.Mode=SAI_A_AsyncSlave
PE4.Signal=SAI1_FS_A
PE5.Mode=SAI_A_AsyncSlave
PE5.Signal=SAI1_SCK_A
PE6.Mode=SAI_A_AsyncSlave
PE6.Signal=SAI1_SD_A
RCC.SYSCLKFreq_VALUE=500000000
RCC.SYSCLKSource=RCC_SYSCLKSOURCE_PLLCLK
board=custom

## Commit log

2023-01-06 Working on initial code layout
2023-01-06 Updates to code
2023-01-06 Adding main Amplifier class
2023-01-10 Updating basic code
2023-01-10 Working on I2C interface
2023-01-19 Updates for encoders
2023-01-21 Almost there
2023-01-21 Triangle beep works
2023-01-21 Test
2023-01-22 IUpdatew
2023-01-24 Fixed issue with start up audio not working.. added bitbanging
2023-01-26 Rewrote LCD
2023-09-17 Checking in AC relay
2023-10-03 Updating Main Project
2023-10-03 Removing DS_Store
2023-10-03 ADding screenshot
2023-10-03 Screenshot
2023-10-03 dding sreenshot
2023-10-03 Adding base images
2023-10-03 Adding images
2023-10-03 Updated ESP32
2023-10-03 PCB updates
2023-10-03 Microprocessor
2023-10-03 Updates for all readmes
2023-10-04 Removing gerbers and backups
2023-10-04 Updating file structure
2023-10-04 KiCAD 7 updates
2023-10-17 Major updates
2023-10-21 Adding 5.1 vs 2.1 speaker mode
2023-10-26 Dolby Working
2023-10-27 Have some sound, doesn’t sound great though
2023-10-27 Kind of works
2023-10-27 Dolby mostly working
2023-10-27 Updates for dolby digital
2023-10-27 Stop and start routines for dolby digital
2023-10-31 Added button debounce code
2023-10-31 Audio improvements
2023-11-01 Adding code
2023-11-04 More updates
2023-11-05 Mostly working
2023-11-05 Switch to I2S
2024-11-29 Updating amplifier
2024-11-30 Moving
2024-12-01 Adding new PCBs and new IR remote code
2024-12-01 Updating readme
2024-12-03 Audio working
2024-12-05 Updating license
2024-12-08 Fixing audio issues, leave TRUNC off and at 24 bits
2024-12-09 Working?
2024-12-21 Updates to amplifer
2024-12-31 Updating project code
2024-12-31 Moving files
2024-12-31 Working on dsp code
2025-01-01 Update to library
2025-01-01 Updating gitignore
2025-01-01 Adding circular buffer
2025-01-01 Hooking up I2S
2025-01-02 Replacing PeakingEQ
2025-01-02 Working
2025-01-03 Updates to main code
